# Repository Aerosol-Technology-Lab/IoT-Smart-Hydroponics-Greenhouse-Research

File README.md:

# IoT-Smart-Hydroponics-Greenhouse-Research
## phSensor Sensor test
Tests for pH sensor

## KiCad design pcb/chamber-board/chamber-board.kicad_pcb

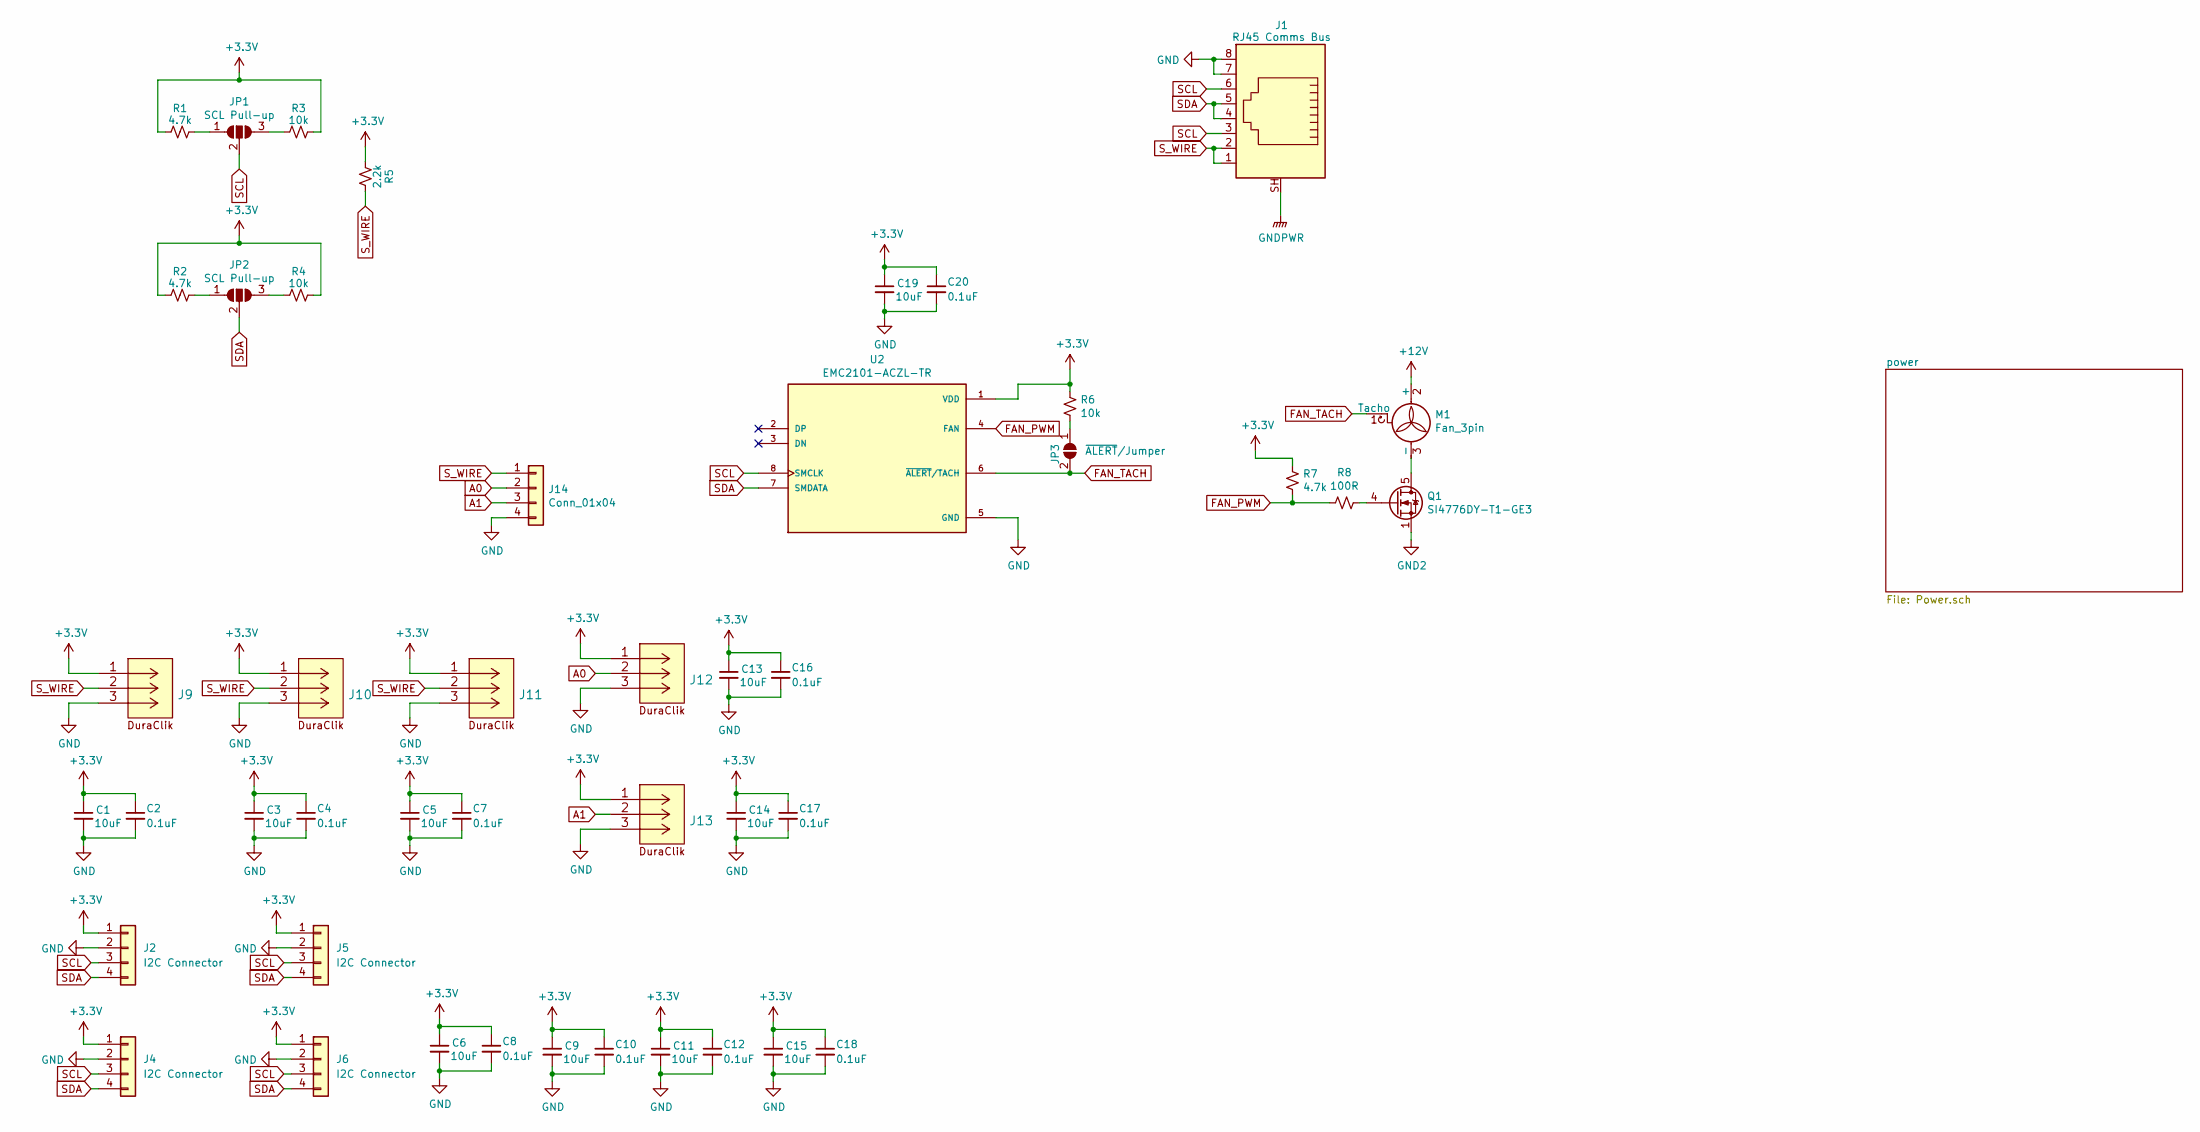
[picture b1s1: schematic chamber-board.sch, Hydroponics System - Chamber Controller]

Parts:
C1, C3, C5, C6, C9, C11, C13, C14, C15, C19: 10uF; C_0805_2012Metric
C2, C4, C7, C8, C10, C12, C16, C17, C18, C20: 0.1uF; C_0603_1608Metric
J1: RJ45 Comms Bus; MTJ-889X1-FSE(RJ45)
J2, J4, J5, J6: I2C Connector; duraclik-4pos
J9, J10, J11, J12, J13: 5023520300(DuraClik-3pos); duraclik-3pos
J14: Conn_01x04; PinHeader_1x04_P2.54mm_Vertical
JP1, JP2: SCL Pull-up; SolderJumper-3_P2.0mm_Open_TrianglePad1.0x1.5mm
JP3: ~ALERT~/Jumper; SolderJumper-2_P1.3mm_Open_TrianglePad1.0x1.5mm
M1: Fan_3pin; 3pin-fanheader
Q1: SI4776DY-T1-GE3
R1, R2, R7: 4.7k; R_0603_1608Metric
R3, R4, R6: 10k; R_0603_1608Metric
R5: 2.2k; R_0603_1608Metric
R8: 100R; R_0603_1608Metric
U2: EMC2101-ACZL-TR; PARTREV 2.54(06-16-09)

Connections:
+3V3: C1.1, C2.1, C3.1, C4.1, C5.1, C6.1, C7.1, C8.1, C9.1, C10.1, C11.1, C12.1, C13.1, C14.1, C15.1, C16.1, C17.1, C18.1, C19.1, C20.1, J2.1, J4.1, J5.1, J6.1, J9.1, J10.1, J11.1, J12.1, J13.1, R1.2, R2.2, R3.1, R4.1, R5.2, R6.1, R7.1, U2.1 (VDD); also elsewhere on the board
+12V: M1.2 (+); also elsewhere on the board
A0: J12.2, J14.2
A1: J13.2, J14.3
FAN_PWM: R7.2, R8.2, U2.4 (FAN)
FAN_TACH: JP3.2 (B), M1.1 (Tacho), U2.6 (~ALERT~/TACH)
GND: C1.2, C2.2, C3.2, C4.2, C5.2, C6.2, C7.2, C8.2, C9.2, C10.2, C11.2, C12.2, C13.2, C14.2, C15.2, C16.2, C17.2, C18.2, C19.2, C20.2, J1.7, J1.8, J2.2, J4.2, J5.2, J6.2, J9.3, J10.3, J11.3, J12.3, J13.3, J14.4, U2.5 (GND); also elsewhere on the board
GND2: Q1.1 (S), Q1.2 (S), Q1.3 (S); also elsewhere on the board
GNDPWR: J1.SH; also elsewhere on the board
unnamed: JP1.1 (A), R1.1
unnamed: JP1.3 (B), R3.2
unnamed: JP2.1 (A), R2.1
unnamed: JP2.3 (B), R4.2
unnamed: JP3.1 (A), R6.2
unnamed: M1.3 (-), Q1.5 (D), Q1.6 (D), Q1.7 (D), Q1.8 (D)
unnamed: Q1.4 (G), R8.1
SCL: J1.3, J1.6, J2.3, J4.3, J5.3, J6.3, JP1.2 (C), U2.8 (SMCLK)
SDA: J1.4, J1.5, J2.4, J4.4, J5.4, J6.4, JP2.2 (C), U2.7 (SMDATA)
S_WIRE: J1.1, J1.2, J9.2, J10.2, J11.2, J14.1, R5.1

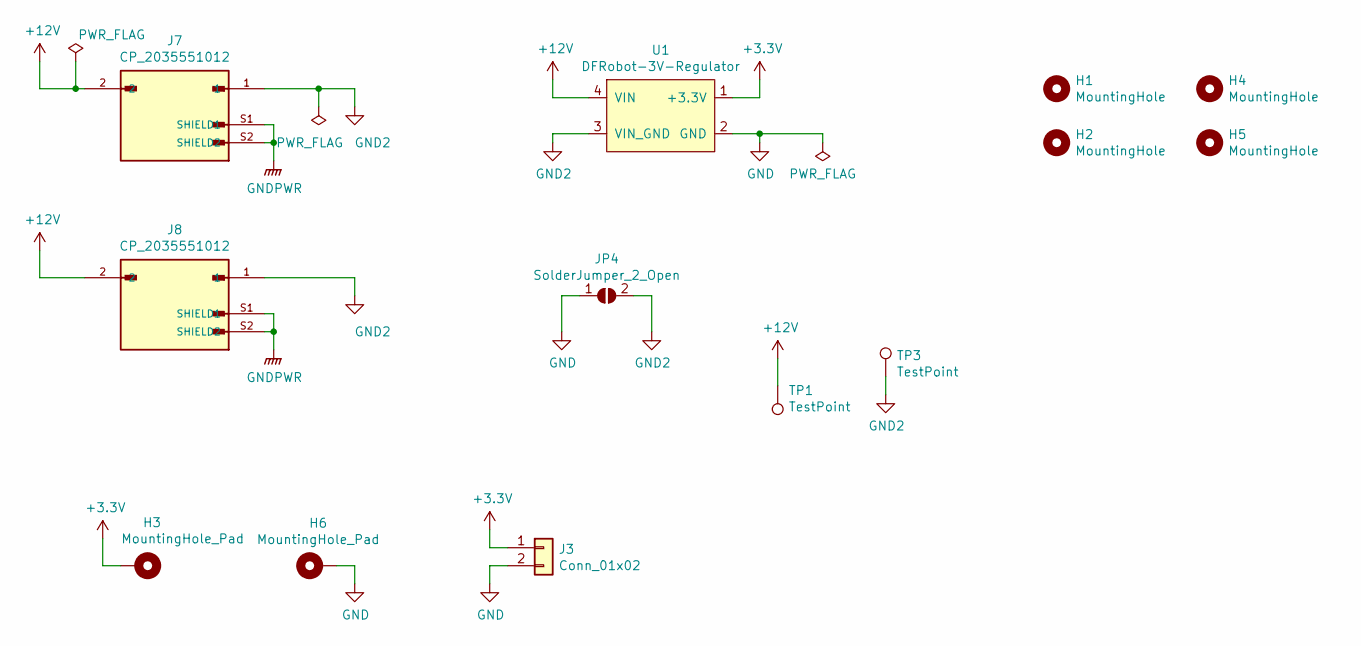
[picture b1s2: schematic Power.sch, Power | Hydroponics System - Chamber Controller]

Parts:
H1, H2, H4, H5: MountingHole; MountingHole_3.2mm_M3_DIN965_Pad_TopBottom
H3, H6: MountingHole_Pad; MountingHole_4.3mm_M4_Pad_Via
J3: Conn_01x02; PinSocket_1x02_P2.54mm_Vertical
J7, J8: CP_2035551012; MOLEX_2035551012; PARTREV A1
JP4: SolderJumper_2_Open; SolderJumper-2_P1.3mm_Open_Pad1.0x1.5mm
TP1, TP3: TestPoint; TestPoint_Pad_D1.5mm
U1: DFRobot-3V-Regulator; DFRobot-3VRegulator

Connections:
+3V3: H3.1, J3.1, U1.1 (+3.3V); also elsewhere on the board
+12V: J7.2, J8.2, TP1.1, U1.4 (VIN); also elsewhere on the board
GND: H6.1, J3.2, JP4.1 (A), U1.2 (GND); also elsewhere on the board
GND2: J7.1, J8.1, JP4.2 (B), TP3.1, U1.3 (VIN_GND); also elsewhere on the board
GNDPWR: J7.S1 (SHIELD1), J7.S2 (SHIELD2), J8.S1 (SHIELD1), J8.S2 (SHIELD2); also elsewhere on the board

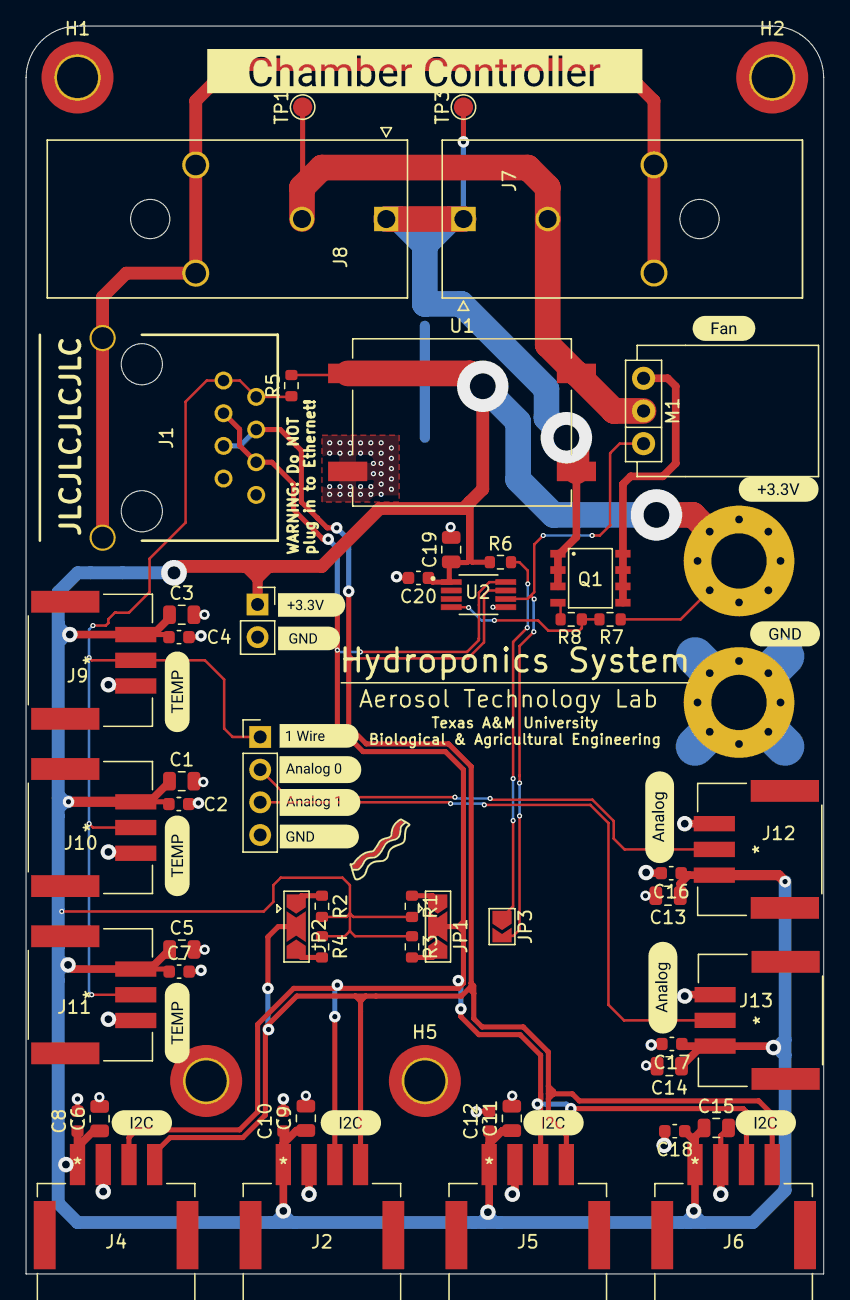
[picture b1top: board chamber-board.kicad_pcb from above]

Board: 2 copper layers, 62.0 x 97.0 mm, 77 parts (1 on the bottom side), 19 nets.

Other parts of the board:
kibuzzard-61722B24, kibuzzard-61722E00, kibuzzard-61722E00#2, kibuzzard-61722EB4, kibuzzard-61722EB4#2, kibuzzard-61722EB4#3, kibuzzard-61722F03, kibuzzard-61722F03#2, kibuzzard-61722F03#3, kibuzzard-61722F03#4, kibuzzard-61722F58, kibuzzard-61722FB7, kibuzzard-61722FC6, kibuzzard-61723AEA, kibuzzard-61723AEE, kibuzzard-61723AF5, kibuzzard-61723AFD, kibuzzard-617232DF, kibuzzard-617232F2: G***; label

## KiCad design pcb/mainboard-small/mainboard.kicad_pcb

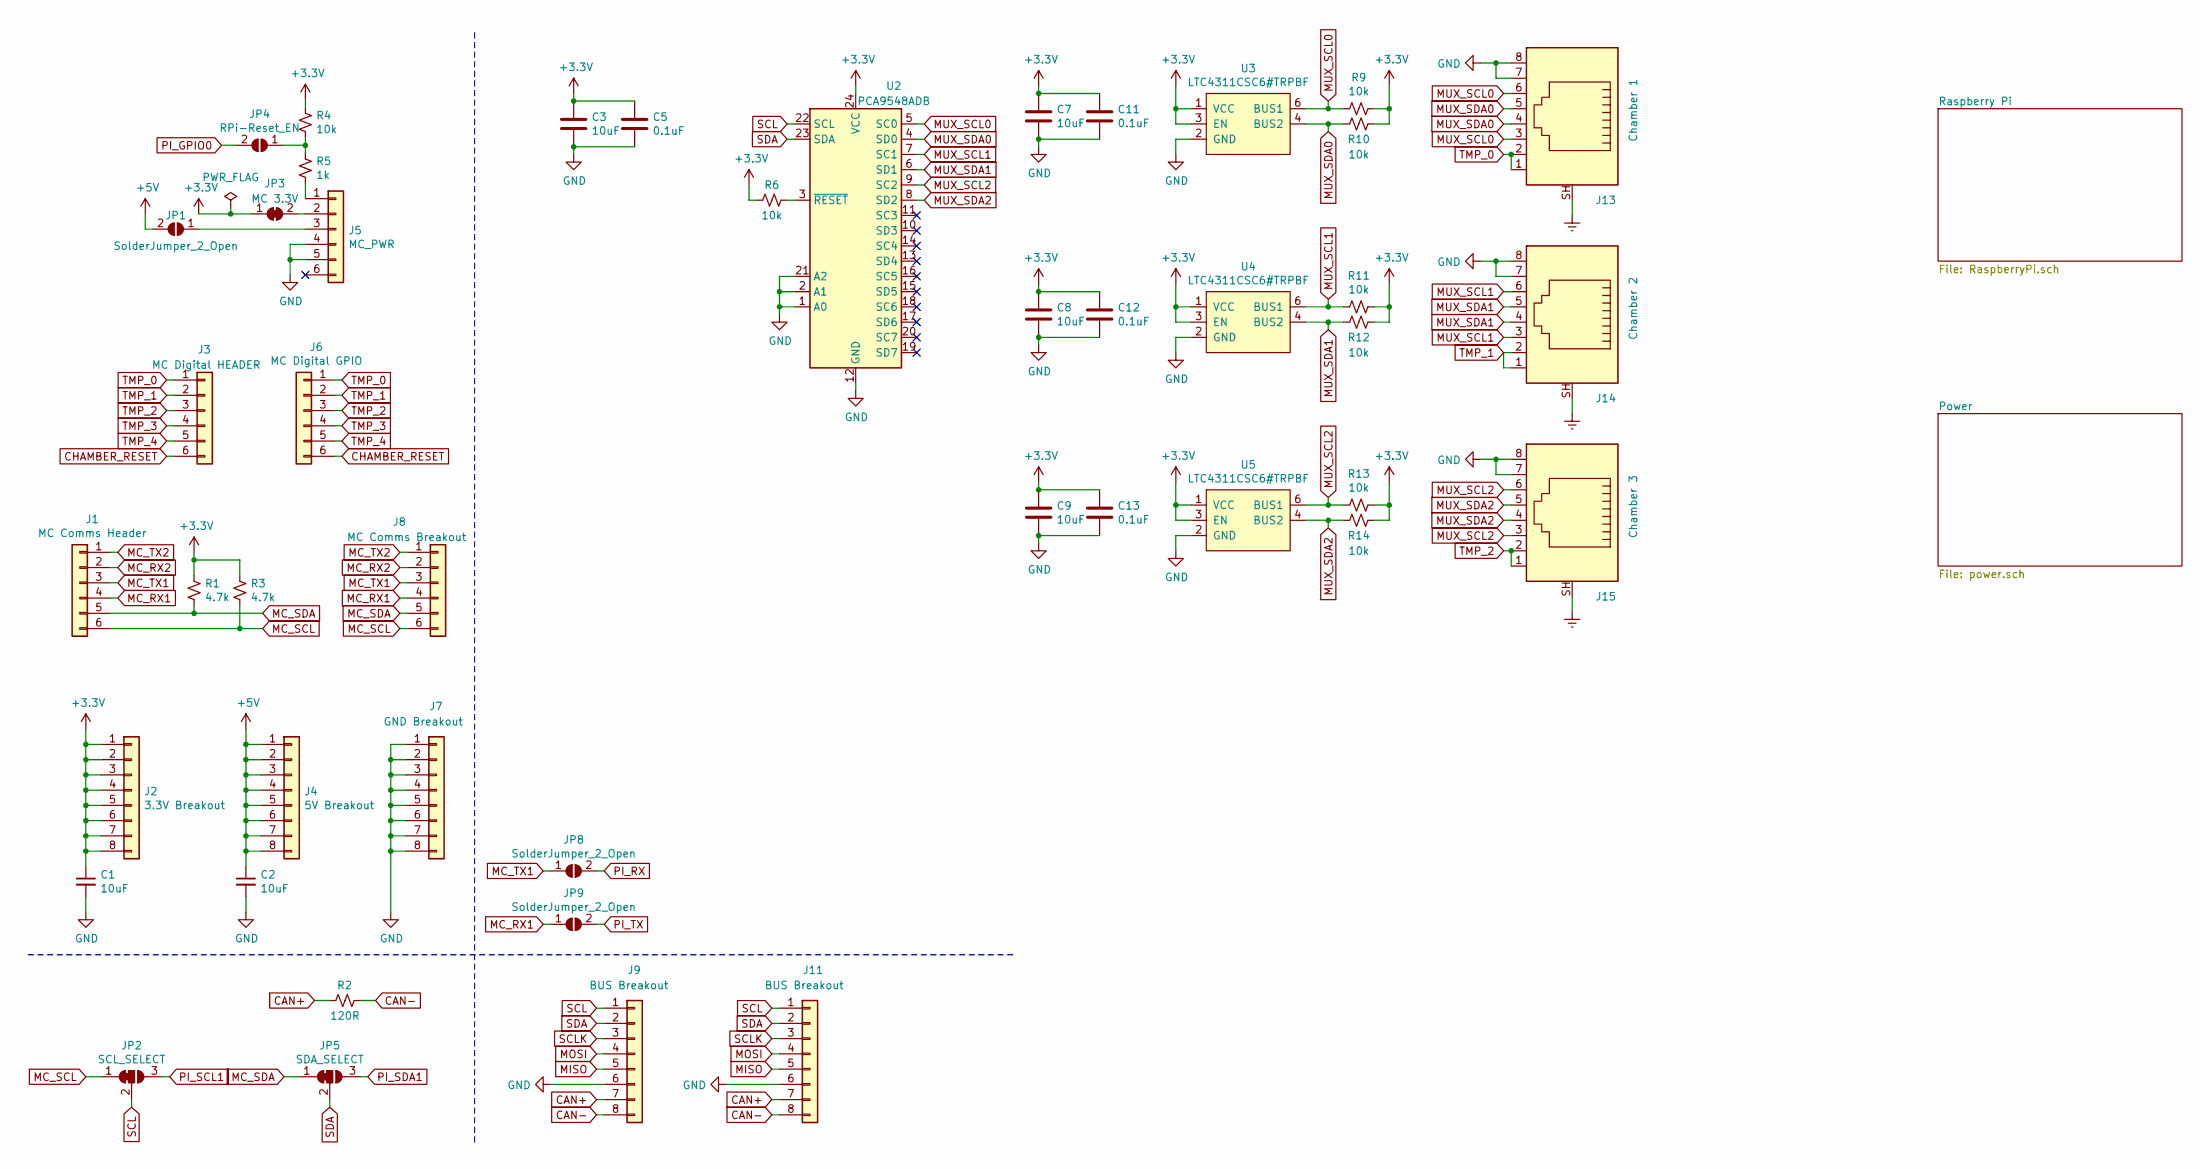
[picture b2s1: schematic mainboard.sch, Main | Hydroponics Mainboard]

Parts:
C1, C2, C3, C7, C8, C9: 10uF; C_0805_2012Metric
C5, C11, C12, C13: 0.1uF; C_0603_1608Metric
J1: MC Comms Header; PinSocket_1x06_P2.54mm_Vertical
J2: 3.3V Breakout; PinSocket_1x08_P2.54mm_Vertical
J3: MC Digital HEADER; PinSocket_1x06_P2.54mm_Vertical
J4: 5V Breakout; PinSocket_1x08_P2.54mm_Vertical
J5: MC_PWR; PinHeader_1x06_P2.54mm_Vertical
J6: MC Digital GPIO; PinSocket_1x06_P2.54mm_Vertical
J7: GND Breakout; PinSocket_1x08_P2.54mm_Vertical
J8: MC Comms Breakout; PinHeader_1x06_P2.54mm_Vertical
J9, J11: BUS Breakout; PinHeader_2x04_P2.54mm_Vertical
J13: Chamber 1; MTJ-889X1-FSE(RJ45)
J14: Chamber 2; MTJ-889X1-FSE(RJ45)
J15: Chamber 3; MTJ-889X1-FSE(RJ45)
JP1: SolderJumper_2_Open; SolderJumper-2_P1.3mm_Open_TrianglePad1.0x1.5mm
JP2: SCL_SELECT; SolderJumper-3_P1.3mm_Bridged12_Pad1.0x1.5mm
JP3: MC 3.3V; SolderJumper-2_P1.3mm_Bridged2Bar_Pad1.0x1.5mm
JP4: RPi-Reset_EN; SolderJumper-2_P1.3mm_Open_TrianglePad1.0x1.5mm
JP5: SDA_SELECT; SolderJumper-3_P1.3mm_Bridged12_Pad1.0x1.5mm
JP8, JP9: SolderJumper_2_Open; SolderJumper-2_P1.3mm_Open_Pad1.0x1.5mm
R1, R3: 4.7k; R_0603_1608Metric
R2: 120R; R_0603_1608Metric
R4, R6, R9, R10, R11, R12, R13, R14: 10k; R_0603_1608Metric
R5: 1k; R_0603_1608Metric
U2: PCA9548ADB; SSOP-24_5.3x8.2mm_P0.65mm
U3, U4, U5: LTC4311CSC6#TRPBF; SOT-363_SC-70-6

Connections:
+3V3: C1.1, C3.1, C5.1, C7.1, C8.1, C9.1, C11.1, C12.1, C13.1, J2.1, J2.2, J2.3, J2.4, J2.5, J2.6, J2.7, J2.8, JP3.1 (A), R1.1, R3.1, R4.1, R6.2, R9.1, R10.1, R11.1, R12.1, R13.1, R14.1, U2.24 (VCC), U3.1 (VCC), U3.3 (EN), U4.1 (VCC), U4.3 (EN), U5.1 (VCC), U5.3 (EN); also elsewhere on the board
+5V: C2.1, J4.1, J4.2, J4.3, J4.4, J4.5, J4.6, J4.7, J4.8, JP1.2 (B); also elsewhere on the board
CAN+: J9.7, J11.7, R2.1
CAN-: J9.8, J11.8, R2.2
CHAMBER_RESET: J3.6, J6.6; also elsewhere on the board
Earth: J13.SH, J14.SH, J15.SH; also elsewhere on the board
GND: C1.2, C2.2, C3.2, C5.2, C7.2, C8.2, C9.2, C11.2, C12.2, C13.2, J5.4, J5.5, J7.1, J7.2, J7.3, J7.4, J7.5, J7.6, J7.7, J7.8, J9.6, J11.6, J13.7, J13.8, J14.7, J14.8, J15.7, J15.8, U2.1 (A0), U2.2 (A1), U2.12 (GND), U2.21 (A2), U3.2 (GND), U3.5 (GND), U4.2 (GND), U4.5 (GND), U5.2 (GND), U5.5 (GND); also elsewhere on the board
MC_RX1: J1.4, J8.4, JP9.1 (A)
MC_RX2: J1.2, J8.2
MC_SCL: J1.6, J8.6, JP2.1 (A), R3.2
MC_SDA: J1.5, J8.5, JP5.1 (A), R1.2
MC_TX1: J1.3, J8.3, JP8.1 (A)
MC_TX2: J1.1, J8.1
MISO: J9.5, J11.5
MOSI: J9.4, J11.4
MUX_SCL0: J13.3, J13.6, R9.2, U2.5 (SC0), U3.6 (BUS1)
MUX_SCL1: J14.3, J14.6, R11.2, U2.7 (SC1), U4.6 (BUS1)
MUX_SCL2: J15.3, J15.6, R13.2, U2.9 (SC2), U5.6 (BUS1)
MUX_SDA0: J13.4, J13.5, R10.2, U2.4 (SD0), U3.4 (BUS2)
MUX_SDA1: J14.4, J14.5, R12.2, U2.6 (SD1), U4.4 (BUS2)
MUX_SDA2: J15.4, J15.5, R14.2, U2.8 (SD2), U5.4 (BUS2)
unnamed: J5.1, R5.2
unnamed: J5.2, JP3.2 (B)
unnamed: J5.3, JP1.1 (A)
unnamed: JP4.1 (A), R4.2, R5.1
unnamed: R6.1, U2.3 (~RESET)
PI_GPIO0: JP4.2 (B); also elsewhere on the board
PI_RX: JP8.2 (B); also elsewhere on the board
PI_SCL1: JP2.3 (B); also elsewhere on the board
PI_SDA1: JP5.3 (B); also elsewhere on the board
PI_TX: JP9.2 (B); also elsewhere on the board
SCL: J9.1, J11.1, JP2.2 (C), U2.22 (SCL)
SCLK: J9.3, J11.3
SDA: J9.2, J11.2, JP5.2 (C), U2.23 (SDA)
TMP_0: J3.1, J6.1, J13.1, J13.2
TMP_1: J3.2, J6.2, J14.1, J14.2
TMP_2: J3.3, J6.3, J15.1, J15.2
TMP_3: J3.4, J6.4
TMP_4: J3.5, J6.5

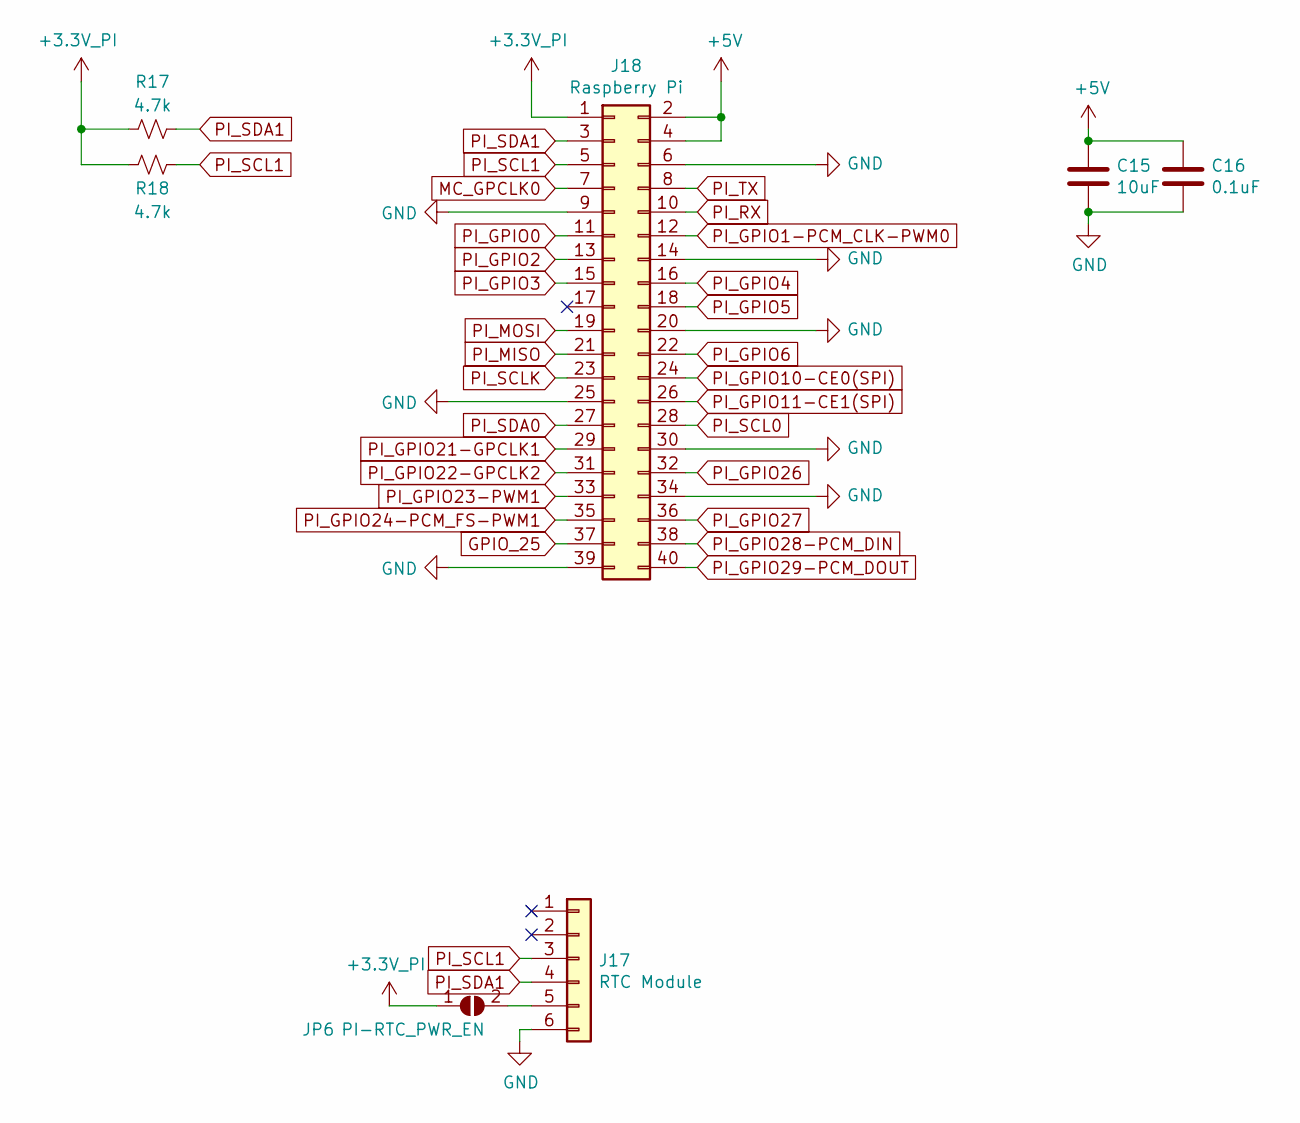
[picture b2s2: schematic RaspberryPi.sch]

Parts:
C15: 10uF; C_0603_1608Metric
C16: 0.1uF; C_0603_1608Metric
J17: RTC Module; PinSocket_1x06_P2.54mm_Vertical
J18: Raspberry Pi; IDC-Header_2x20_P2.54mm_Vertical
JP6: PI-RTC_PWR_EN; SolderJumper-2_P1.3mm_Open_TrianglePad1.0x1.5mm
R17, R18: 4.7k; R_0603_1608Metric

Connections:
+5V: C15.1, C16.1, J18.2, J18.4; also elsewhere on the board
GND: C15.2, C16.2, J17.6, J18.6, J18.9, J18.14, J18.20, J18.25, J18.30, J18.34, J18.39; also elsewhere on the board
unnamed: J17.5, JP6.2 (B)
PI_GPIO0: J18.11; also elsewhere on the board
PI_RX: J18.10; also elsewhere on the board
PI_SCL1: J17.3, J18.5, R18.1; also elsewhere on the board
PI_SDA1: J17.4, J18.3, R17.1; also elsewhere on the board
PI_TX: J18.8; also elsewhere on the board
~: J18.1, JP6.1 (A), R17.2, R18.2

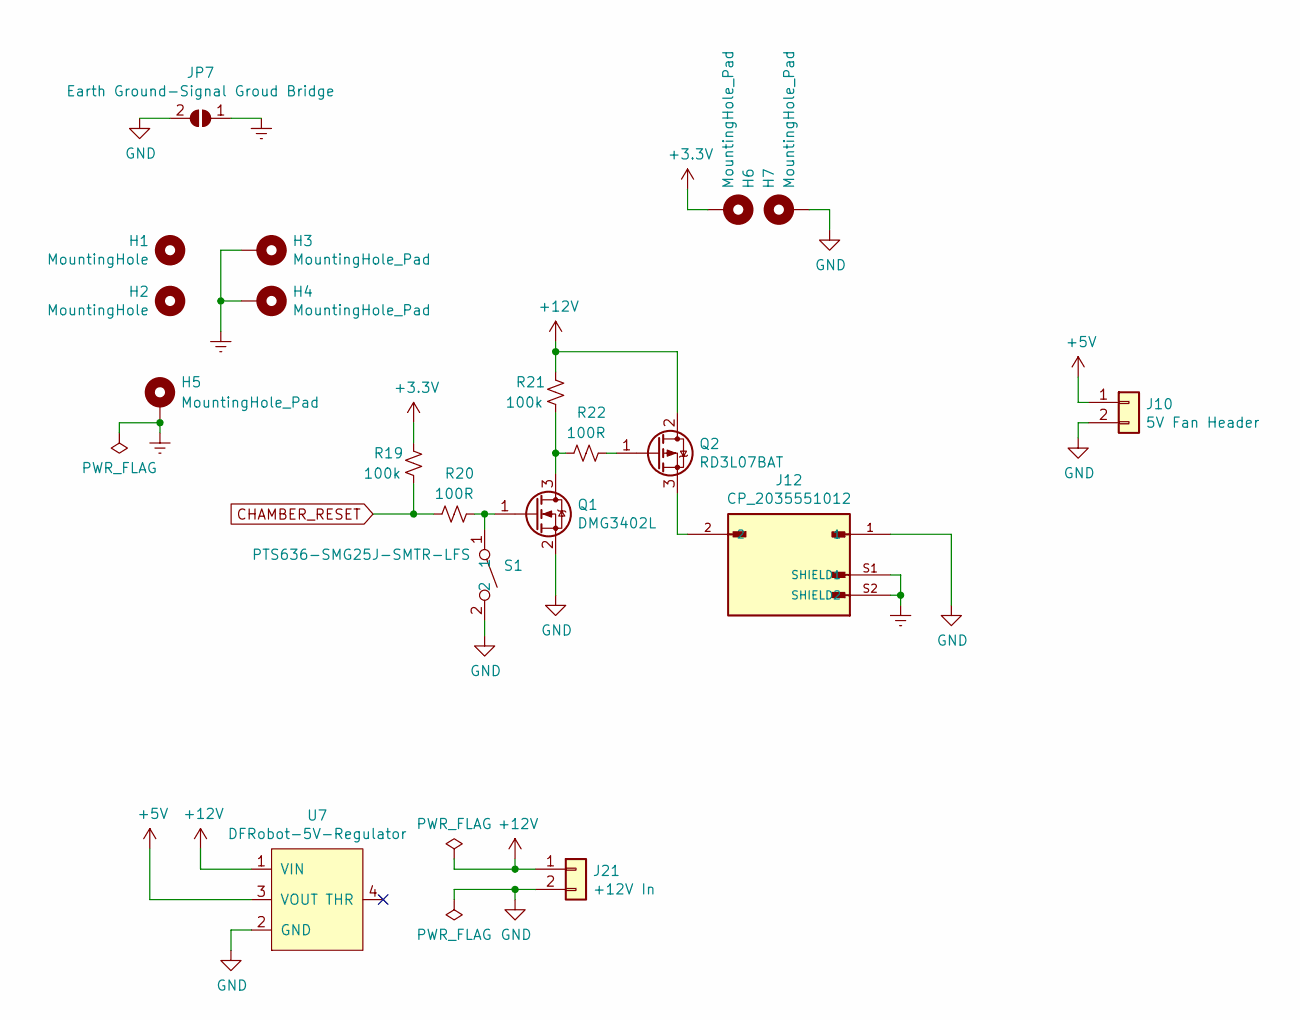
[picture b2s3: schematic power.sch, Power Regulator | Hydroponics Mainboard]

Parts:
H1, H2: MountingHole; MountingHole_3.2mm_M3_ISO7380_Pad_TopOnly
H3, H4, H5: MountingHole_Pad; MountingHole_3.2mm_M3_Pad_Via
H6, H7: MountingHole_Pad; MountingHole_4.3mm_M4_Pad_Via
J10: 5V Fan Header; PinHeader_1x02_P2.54mm_Vertical
J12: CP_2035551012; MOLEX_2035551012; PARTREV A1
J21: +12V In; YK7010223000G(2POS-Terminal-Block)
JP7: Earth Ground-Signal Groud Bridge; SolderJumper-2_P1.3mm_Open_TrianglePad1.0x1.5mm
Q1: DMG3402L; SOT-23
Q2: RD3L07BAT; TO-252-2
R19, R21: 100k; R_0603_1608Metric
R20, R22: 100R; R_0603_1608Metric
S1: PTS636-SMG25J-SMTR-LFS; PTS636SK50SMTRLFS
U7: DFRobot-5V-Regulator

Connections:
+3V3: H6.1, R19.1; also elsewhere on the board
+5V: J10.1, U7.3 (VOUT); also elsewhere on the board
+12V: J21.1, Q2.2 (D), R21.1, U7.1 (VIN)
CHAMBER_RESET: R19.2, R20.2; also elsewhere on the board
Earth: H3.1, H4.1, H5.1, J12.S1 (SHIELD1), J12.S2 (SHIELD2), JP7.1 (A); also elsewhere on the board
GND: H7.1, J10.2, J12.1, J21.2, JP7.2 (B), Q1.2 (S), S1.2, U7.2 (GND); also elsewhere on the board
unnamed: J12.2, Q2.3 (S)
unnamed: Q1.1 (G), R20.1, S1.1
unnamed: Q1.3 (D), R21.2, R22.2
unnamed: Q2.1 (G), R22.1

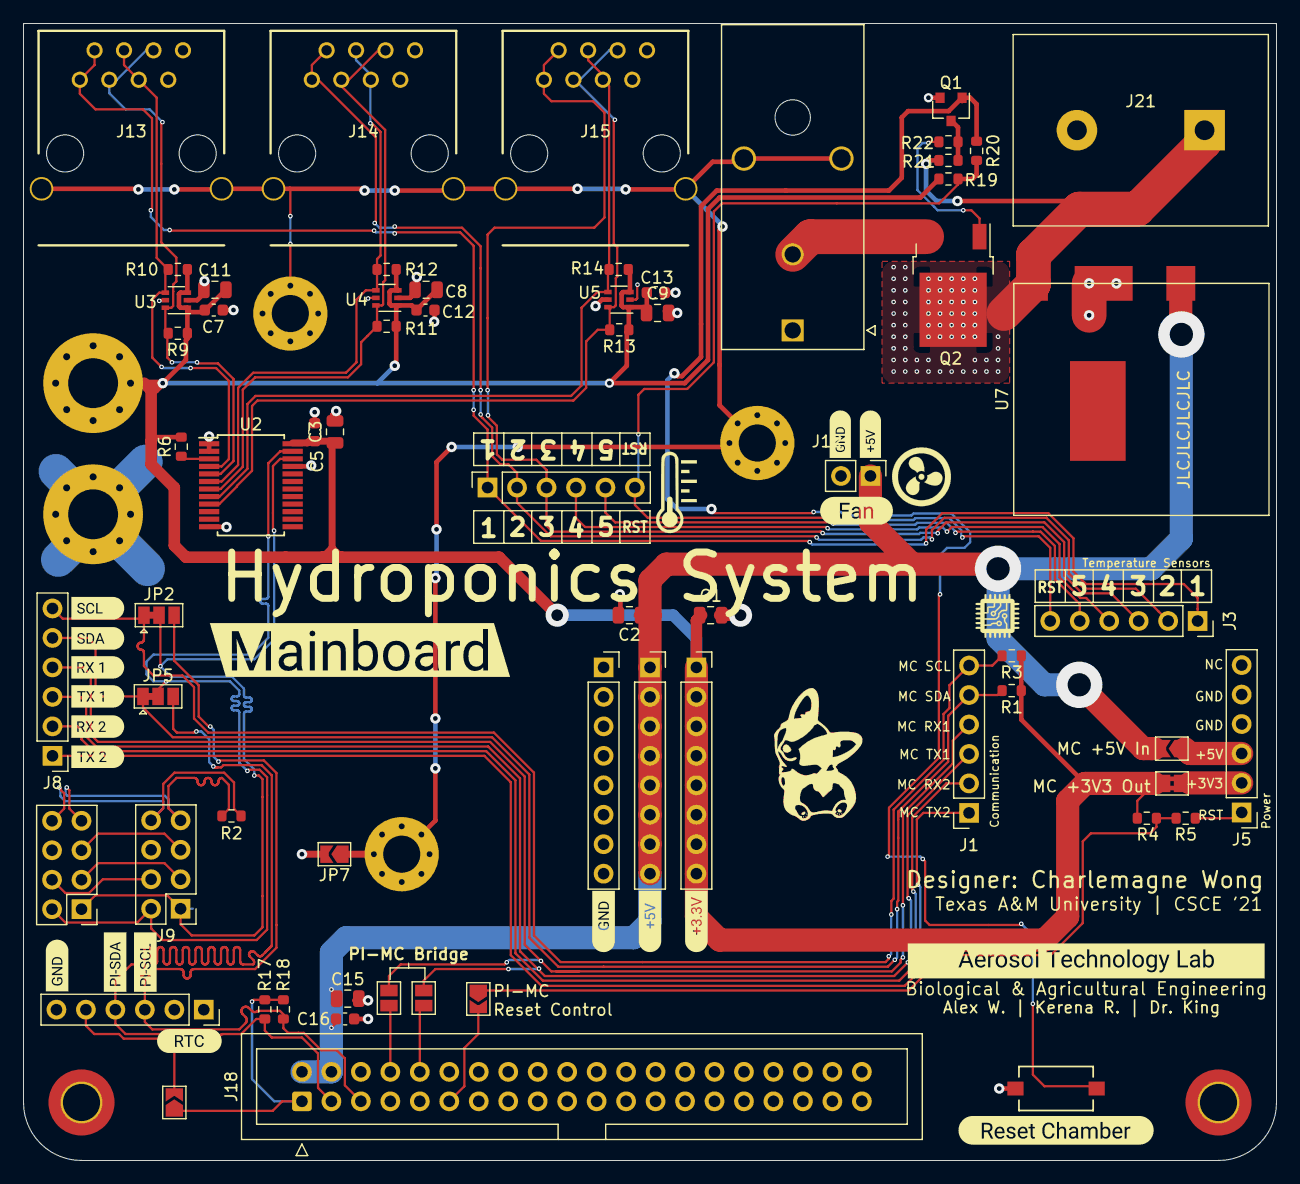
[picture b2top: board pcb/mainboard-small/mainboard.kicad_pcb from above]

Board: 2 copper layers, 108.0 x 98.0 mm, 92 parts (1 on the bottom side), 46 nets.

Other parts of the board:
QR*****: Website
kibuzzard-616F51D1, kibuzzard-6170A1A7, kibuzzard-6170A2EA, kibuzzard-6170A2EF, kibuzzard-6170A2F3, kibuzzard-6170A2F8, kibuzzard-6170A2FD, kibuzzard-6170A21A, kibuzzard-6170A145, kibuzzard-6170A234, kibuzzard-6170A301, kibuzzard-6170BBF0, kibuzzard-6170FF3B, kibuzzard-6170FFCB, kibuzzard-6170FFCF, kibuzzard-61707D3E, kibuzzard-61707D37, kibuzzard-61707DB8, kibuzzard-61710606: G***; label

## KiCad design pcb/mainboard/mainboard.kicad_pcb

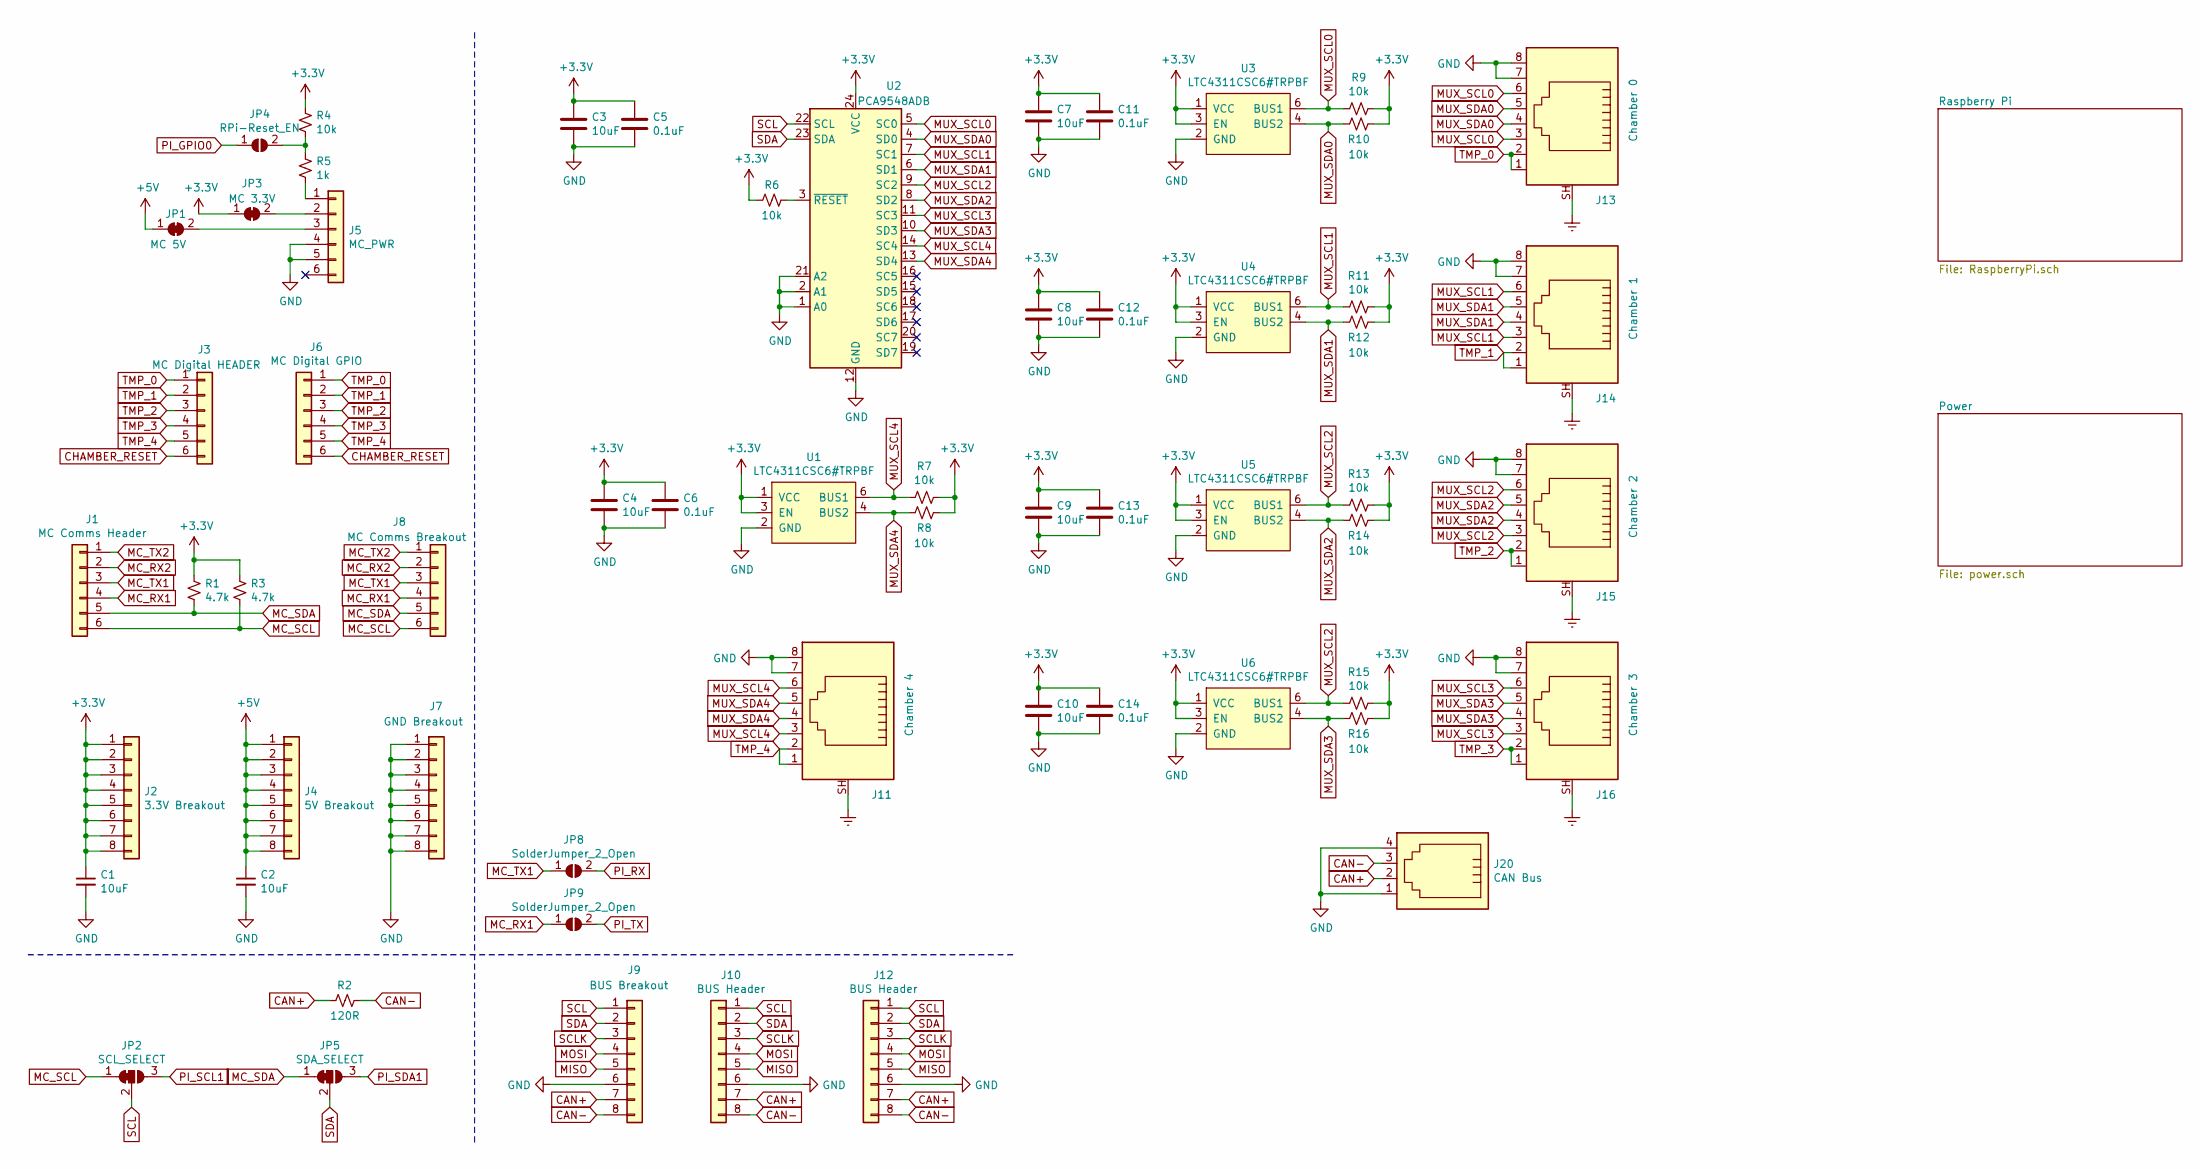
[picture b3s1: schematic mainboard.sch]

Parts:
C1, C2, C3, C4, C7, C8, C9, C10: 10uF; C_0603_1608Metric
C5, C6, C11, C12, C13, C14: 0.1uF; C_0603_1608Metric
J1: MC Comms Header
J2: 3.3V Breakout; PinSocket_1x08_P2.54mm_Vertical
J3: MC Digital HEADER
J4: 5V Breakout; PinSocket_1x08_P2.54mm_Vertical
J5: MC_PWR
J6: MC Digital GPIO
J7: GND Breakout; PinSocket_1x08_P2.54mm_Vertical
J8: MC Comms Breakout; PinHeader_1x06_P2.54mm_Vertical
J9: BUS Breakout; PinSocket_1x08_P2.54mm_Vertical
J10, J12: BUS Header
J11: Chamber 4; MTJ-889X1-FSE(RJ45)
J13: Chamber 0; MTJ-889X1-FSE(RJ45)
J14: Chamber 1; MTJ-889X1-FSE(RJ45)
J15: Chamber 2; MTJ-889X1-FSE(RJ45)
J16: Chamber 3; MTJ-889X1-FSE(RJ45)
J20: CAN Bus; RJ22
JP1: MC 5V; SolderJumper-2_P1.3mm_Bridged_Pad1.0x1.5mm
JP2: SCL_SELECT; SolderJumper-3_P1.3mm_Bridged12_Pad1.0x1.5mm
JP3: MC 3.3V; SolderJumper-2_P1.3mm_Bridged2Bar_Pad1.0x1.5mm
JP4: RPi-Reset_EN; SolderJumper-2_P1.3mm_Open_TrianglePad1.0x1.5mm
JP5: SDA_SELECT; SolderJumper-3_P1.3mm_Bridged12_Pad1.0x1.5mm
JP8, JP9: SolderJumper_2_Open; SolderJumper-2_P1.3mm_Open_Pad1.0x1.5mm
R1, R3: 4.7k; R_0603_1608Metric
R2: 120R; R_0603_1608Metric
R4, R6, R7, R8, R9, R10, R11, R12, R13, R14, R15, R16: 10k; R_0603_1608Metric
R5: 1k; R_0603_1608Metric
U1, U3, U4, U5, U6: LTC4311CSC6#TRPBF; SOT-363_SC-70-6
U2: PCA9548ADB; SSOP-24_5.3x8.2mm_P0.65mm

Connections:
+3V3: C1.1, C3.1, C4.1, C5.1, C6.1, C7.1, C8.1, C9.1, C10.1, C11.1, C12.1, C13.1, C14.1, J2.1, J2.2, J2.3, J2.4, J2.5, J2.6, J2.7, J2.8, JP3.1 (A), R1.1, R3.1, R4.1, R6.2, R7.1, R8.1, R9.1, R10.1, R11.1, R12.1, R13.1, R14.1, R15.1, R16.1, U1.1 (VCC), U1.3 (EN), U2.24 (VCC), U3.1 (VCC), U3.3 (EN), U4.1 (VCC), U4.3 (EN), U5.1 (VCC), U5.3 (EN), U6.1 (VCC), U6.3 (EN); also elsewhere on the board
+5V: C2.1, J4.1, J4.2, J4.3, J4.4, J4.5, J4.6, J4.7, J4.8, JP1.1 (A); also elsewhere on the board
CAN+: J9.7, J10.7, J12.7, J20.2, R2.1
CAN-: J9.8, J10.8, J12.8, J20.3, R2.2
Earth: J11.SH, J13.SH, J14.SH, J15.SH, J16.SH; also elsewhere on the board
GND: C1.2, C2.2, C3.2, C4.2, C5.2, C6.2, C7.2, C8.2, C9.2, C10.2, C11.2, C12.2, C13.2, C14.2, J5.4, J5.5, J7.1, J7.2, J7.3, J7.4, J7.5, J7.6, J7.7, J7.8, J9.6, J10.6, J11.7, J11.8, J12.6, J13.7, J13.8, J14.7, J14.8, J15.7, J15.8, J16.7, J16.8, J20.1, J20.4, U1.2 (GND), U1.5 (GND), U2.1 (A0), U2.2 (A1), U2.12 (GND), U2.21 (A2), U3.2 (GND), U3.5 (GND), U4.2 (GND), U4.5 (GND), U5.2 (GND), U5.5 (GND), U6.2 (GND), U6.5 (GND); also elsewhere on the board
MC_RX1: J1.4, J8.4, JP9.1 (A)
MC_RX2: J1.2, J8.2
MC_SCL: J1.6, J8.6, JP2.1 (A), R3.2
MC_SDA: J1.5, J8.5, JP5.1 (A), R1.2
MC_TX1: J1.3, J8.3, JP8.1 (A)
MC_TX2: J1.1, J8.1
MISO: J9.5, J10.5, J12.5
MOSI: J9.4, J10.4, J12.4
MUX_SCL0: J13.3, J13.6, R9.2, U2.5 (SC0), U3.6 (BUS1)
MUX_SCL1: J14.3, J14.6, R11.2, U2.7 (SC1), U4.6 (BUS1)
MUX_SCL2: J15.3, J15.6, R13.2, R15.2, U2.9 (SC2), U5.6 (BUS1), U6.6 (BUS1)
MUX_SCL3: J16.3, J16.6, U2.11 (SC3)
MUX_SCL4: J11.3, J11.6, R7.2, U1.6 (BUS1), U2.14 (SC4)
MUX_SDA0: J13.4, J13.5, R10.2, U2.4 (SD0), U3.4 (BUS2)
MUX_SDA1: J14.4, J14.5, R12.2, U2.6 (SD1), U4.4 (BUS2)
MUX_SDA2: J15.4, J15.5, R14.2, U2.8 (SD2), U5.4 (BUS2)
MUX_SDA3: J16.4, J16.5, R16.2, U2.10 (SD3), U6.4 (BUS2)
MUX_SDA4: J11.4, J11.5, R8.2, U1.4 (BUS2), U2.13 (SD4)
unnamed: J3.6, J6.6
unnamed: J5.1, R5.2
unnamed: J5.2, JP3.2 (B)
unnamed: J5.3, JP1.2 (B)
unnamed: JP4.2 (B), R4.2, R5.1
unnamed: R6.1, U2.3 (~RESET)
PI_GPIO0: JP4.1 (A); also elsewhere on the board
PI_RX: JP8.2 (B); also elsewhere on the board
PI_SCL1: JP2.3 (B); also elsewhere on the board
PI_SDA1: JP5.3 (B); also elsewhere on the board
PI_TX: JP9.2 (B); also elsewhere on the board
SCL: J9.1, J10.1, J12.1, JP2.2 (C), U2.22 (SCL)
SCLK: J9.3, J10.3, J12.3
SDA: J9.2, J10.2, J12.2, JP5.2 (C), U2.23 (SDA)
TMP_0: J3.1, J6.1, J13.1, J13.2
TMP_1: J3.2, J6.2, J14.1, J14.2
TMP_2: J3.3, J6.3, J15.1, J15.2
TMP_3: J3.4, J6.4, J16.1, J16.2
TMP_4: J3.5, J6.5, J11.1, J11.2

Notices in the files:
parts and their libraries:
Copyright 2021 Accelerated Designs. All rights reserved.
